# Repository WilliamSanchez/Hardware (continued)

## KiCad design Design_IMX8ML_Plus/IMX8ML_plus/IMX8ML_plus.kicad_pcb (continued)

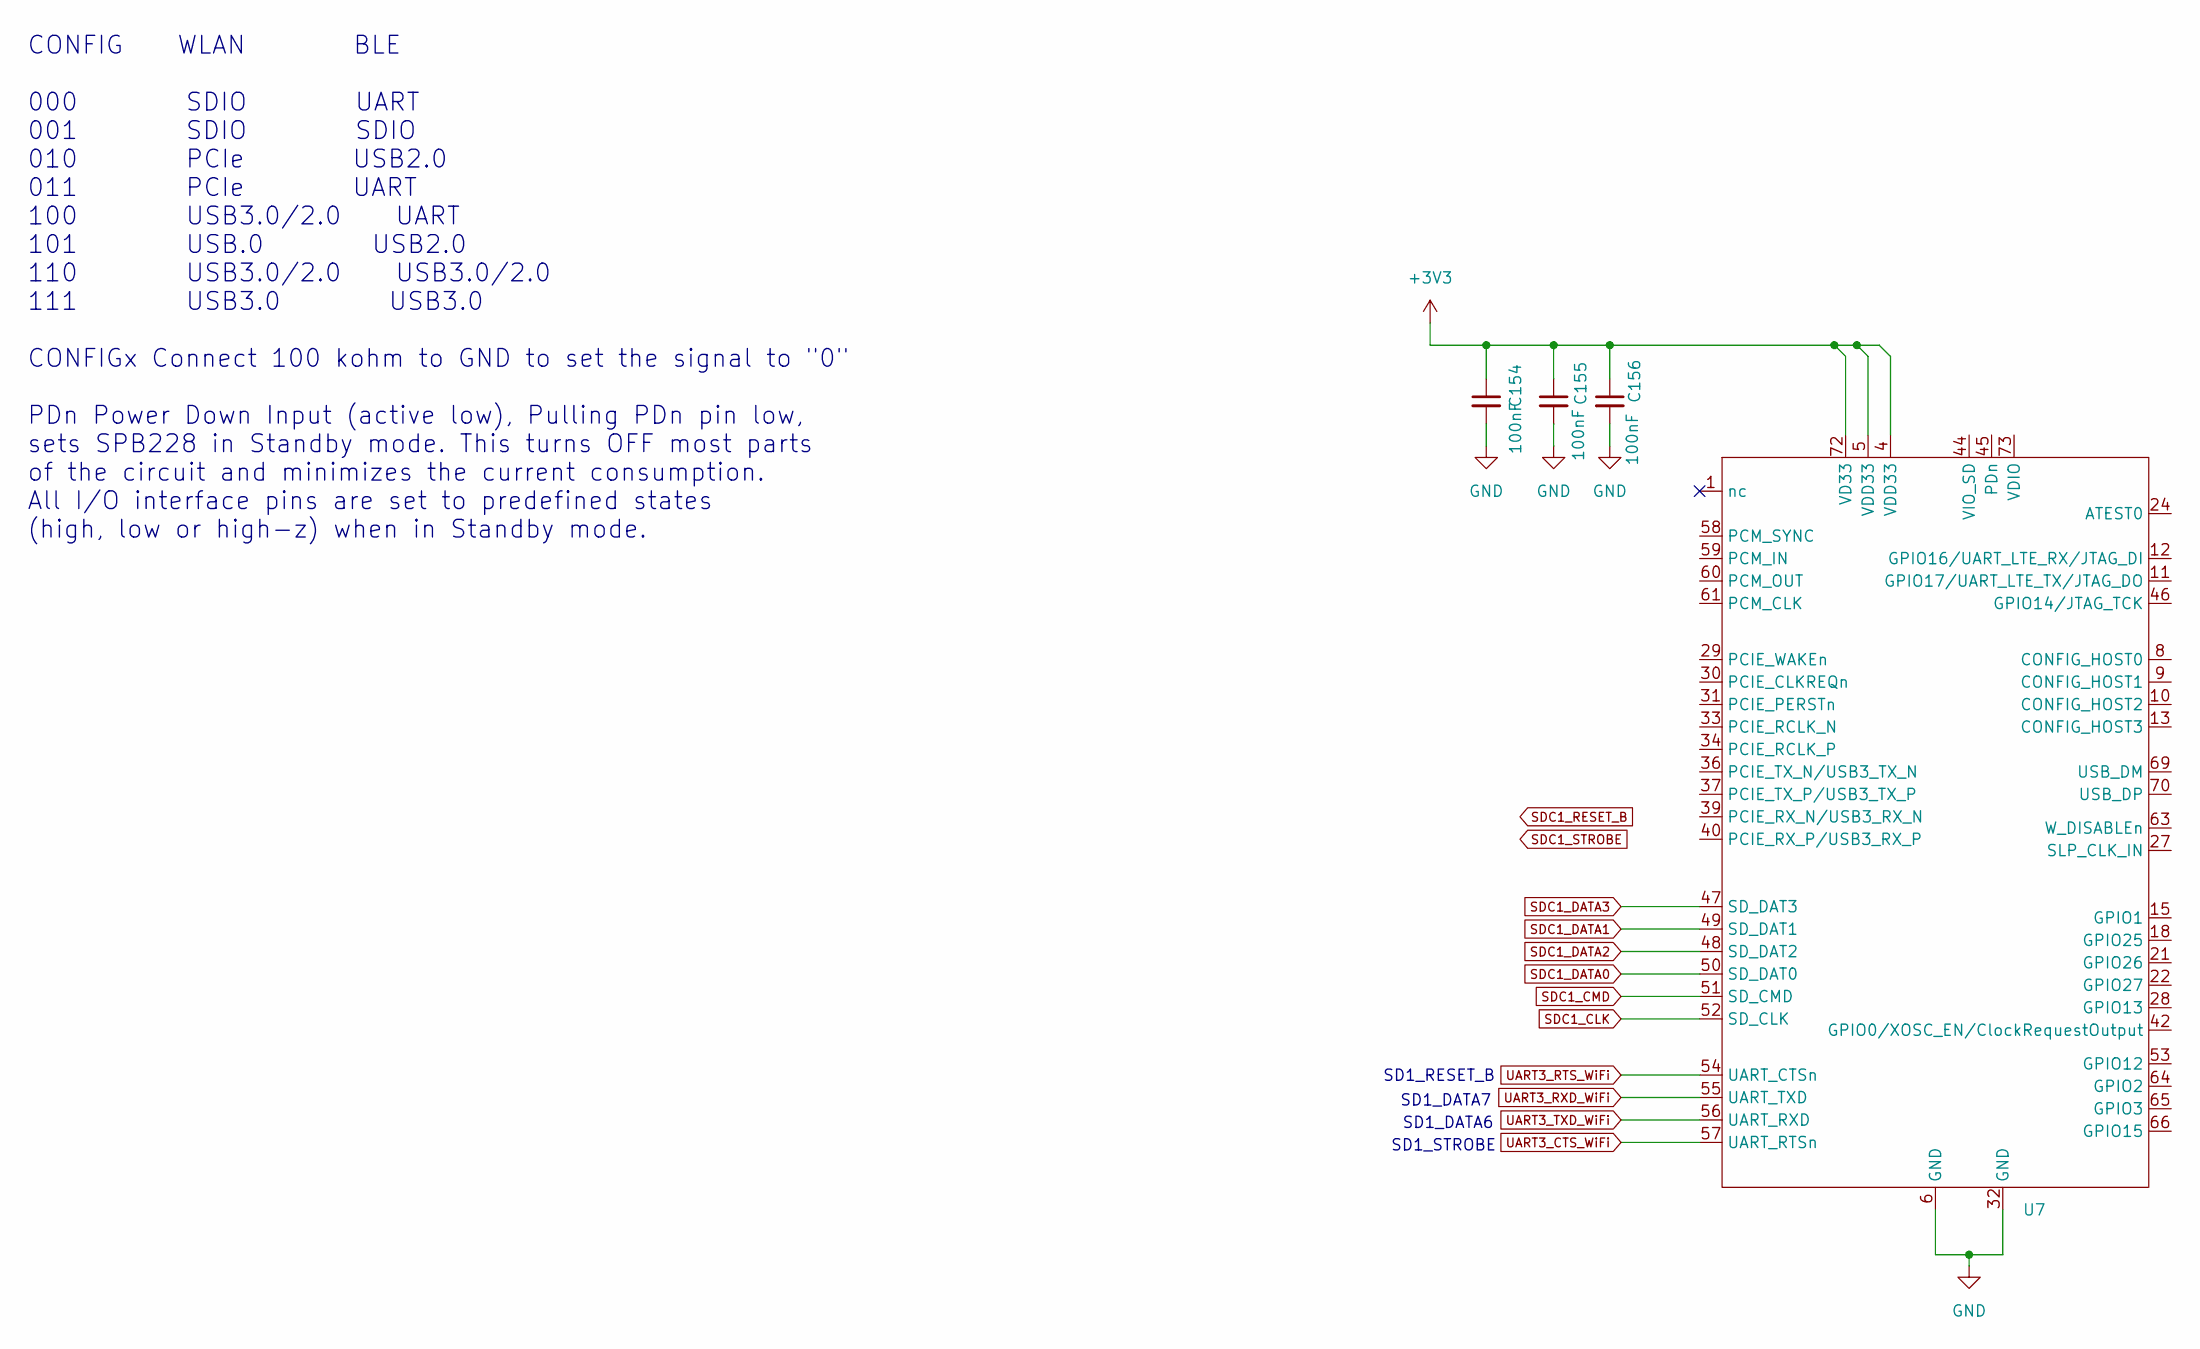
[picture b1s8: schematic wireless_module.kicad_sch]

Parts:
C154, C155, C156: 100nF; C_0201_0603Metric
U7: SPB228-QFN-96_11.55x15.55_Pitch0.5mm

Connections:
+3V3: C154.1, C155.1, C156.1, U7.4 (VDD33), U7.5 (VDD33), U7.72 (VD33); also elsewhere on the board
GND: C154.2, C155.2, C156.2, U7.6 (GND), U7.17 (GND), U7.20 (GND), U7.23 (GND), U7.26 (GND), U7.32 (GND), U7.35 (GND), U7.38 (GND), U7.41 (GND), U7.62 (GND), U7.68 (GND), U7.71 (GND), U7.74 (GND), U7.75 (GND), U7.76 (GND), U7.77 (GND), U7.78 (GND), U7.79 (GND), U7.80 (GND), U7.81 (GND), U7.82 (GND), U7.83 (GND), U7.84 (GND), U7.85 (GND), U7.86 (GND), U7.87 (GND), U7.89 (GND), U7.90 (GND), U7.91 (GND), U7.92 (GND), U7.93 (GND), U7.94 (GND), U7.95 (GND), U7.96 (GND); also elsewhere on the board
SDC1_CLK: U7.52 (SD_CLK); also elsewhere on the board
SDC1_CMD: U7.51 (SD_CMD); also elsewhere on the board
SDC1_DATA0: U7.50 (SD_DAT0); also elsewhere on the board
SDC1_DATA1: U7.49 (SD_DAT1); also elsewhere on the board
SDC1_DATA2: U7.48 (SD_DAT2); also elsewhere on the board
SDC1_DATA3: U7.47 (SD_DAT3); also elsewhere on the board
UART3_CTS_WiFi: U7.57 (UART_RTSn); also elsewhere on the board
UART3_RTS_WiFi: U7.54 (UART_CTSn); also elsewhere on the board
UART3_RXD_WiFi: U7.55 (UART_TXD); also elsewhere on the board
UART3_TXD_WiFi: U7.56 (UART_RXD); also elsewhere on the board

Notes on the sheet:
SD1_DATA7
SD1_RESET_B
SD1_STROBE
SD1_DATA6
CONFIG WLAN BLE 000 SDIO UART 001 SDIO SDIO 010 PCIe USB2.0 011 PCIe UART 100 USB3.0/2.0 UART 101 USB.0 USB2.0 110 USB3.0/2.0 USB3.0/2.0 111 USB3.0 USB3.0 CONFIGx Connect 100 kohm to GND to set the signal to "0" PDn Power Down Input (active low), Pulling PDn pin low, sets SPB228 in Standby mode. Th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

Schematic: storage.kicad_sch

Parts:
C115, C118: 12pF; C_0201_0603Metric
C116, C119, C120, C123, C124, C126, C127: 0.22uF; C_0201_0603Metric
C117: 1uF; C_0201_0603Metric
C121: 4.7uF; C_0402_1005Metric
C122, C125: 10uF; C_0402_1005Metric
C159, C160: 2200pF; C_0201_0603Metric
C161: 18pF; C_0201_0603Metric
D2: LED; LED_0603_1608Metric
Q1: NX3008NBKW,115; SOT-323_SC-70
R10, R11: 100K; R_0201_0603Metric
R12: 8.2K; R_0201_0603Metric
R13, R21: 100K; R_0402_1005Metric
R14: 4.7M; R_0402_1005Metric
R15: 10K; R_0402_1005Metric
R42: 0; R_0402_1005Metric
R43: 550; R_0402_1005Metric
U1: MIMX8ML8CVNKZAB; LFBGA548_SOT2047-1_NXP
U4: SDINBDG4-8G; BGA153C50P14X14_1300X1150X80N
U5: MT25QUxxxxxx1xW7; W-PDFN-8-1EP_6x5mm_P1.27mm_EP3x3mm
Y2: 32.768KHz; C_0504_1310Metric

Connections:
+3V3: R43.1; also elsewhere on the board
/Processor/storage/MIPI_TEST_DNU: C159.1, U1.F24 (MIPI_TEST_DNU)
/Processor/storage/MIPI_VREG1_CAP: C160.1, U1.F18 (MIPI_VREG1_CAP)
/Processor/storage/NAND_DQS: C161.1, R42.2, U1.R26 (NAND_DQS)
/Processor/storage/NAND_READY_B: Q1.1 (G), U1.T28 (NAND_READY_B)
/Processor/storage/QSPIA_DATA0: U1.R25 (NAND_DATA00), U5.5 (DQ0)
/Processor/storage/QSPIA_DATA1: U1.L25 (NAND_DATA01), U5.2 (DQ1)
/Processor/storage/QSPIA_DATA2: U1.L24 (NAND_DATA02), U5.3 (~W/DQ2)
/Processor/storage/QSPIA_DATA3: U1.N24 (NAND_DATA03), U5.7 (~RESET/DQ3)
/Processor/storage/QSPIA_SCLK: U1.N25 (NAND_ALE), U5.6 (C)
/Processor/storage/QSPIA_nSS0: R15.2, U1.L26 (NAND_CE0_B), U5.1 (~S)
/Processor/storage/SD3_CLK: U1.U29 (NAND_WP_B), U4.M6 (CLK)
/Processor/storage/SD3_CMD: U1.U28 (NAND_WE_B), U4.M5 (CMD)
/Processor/storage/SD3_DATA0: U1.P29 (NAND_DATA04), U4.A3 (DAT0)
/Processor/storage/SD3_DATA1: U1.N29 (NAND_DATA05), U4.A4 (DAT1)
/Processor/storage/SD3_DATA2: U1.M29 (NAND_DATA06), U4.A5 (DAT2)
/Processor/storage/SD3_DATA3: U1.R29 (NAND_DATA07), U4.B2 (DAT3)
/Processor/storage/SD3_DATA4: U1.R28 (NAND_RE_B), U4.B3 (DAT4)
/Processor/storage/SD3_DATA5: U1.P28 (NAND_CE2_B), U4.B4 (DAT5)
/Processor/storage/SD3_DATA6: U1.N28 (NAND_CE3_B), U4.B5 (DAT6)
/Processor/storage/SD3_DATA7: U1.M28 (NAND_CLE), U4.B6 (DAT7)
/Processor/storage/SD3_STROBE: U1.T29 (NAND_CE1_B), U4.H5 (RCLK)
CSI1_CLK_N: U1.E22 (MIPI_CSI1_CLK_N); also elsewhere on the board
CSI1_CLK_P: U1.D22 (MIPI_CSI1_CLK_P); also elsewhere on the board
CSI1_D0_N: U1.E18 (MIPI_CSI1_D0_N); also elsewhere on the board
CSI1_D0_P: U1.D18 (MIPI_CSI1_D0_P); also elsewhere on the board
CSI1_D1_N: U1.E20 (MIPI_CSI1_D1_N); also elsewhere on the board
CSI1_D1_P: U1.D20 (MIPI_CSI1_D1_P); also elsewhere on the board
CSI1_D2_N: U1.E24 (MIPI_CSI1_D2_N); also elsewhere on the board
CSI1_D2_P: U1.D24 (MIPI_CSI1_D2_P); also elsewhere on the board
CSI1_D3_N: U1.E26 (MIPI_CSI1_D3_N); also elsewhere on the board
CSI1_D3_P: U1.D26 (MIPI_CSI1_D3_P); also elsewhere on the board
CSI2_CLK_N: U1.B23 (MIPI_CSI2_CLK_N); also elsewhere on the board
CSI2_CLK_P: U1.A23 (MIPI_CSI2_CLK_P); also elsewhere on the board
CSI2_D0_N: U1.B25 (MIPI_CSI2_D0_N); also elsewhere on the board
CSI2_D0_P: U1.A25 (MIPI_CSI2_D0_P); also elsewhere on the board
CSI2_D1_N: U1.B24 (MIPI_CSI2_D1_N); also elsewhere on the board
CSI2_D1_P: U1.A24 (MIPI_CSI2_D1_P); also elsewhere on the board
CSI2_D2_N: U1.B22 (MIPI_CSI2_D2_N); also elsewhere on the board
CSI2_D2_P: U1.A22 (MIPI_CSI2_D2_P); also elsewhere on the board
CSI2_D3_N: U1.B21 (MIPI_CSI2_D3_N); also elsewhere on the board
CSI2_D3_P: U1.A21 (MIPI_CSI2_D3_P); also elsewhere on the board
DSI1_CLK_N: U1.B18 (MIPI_DSI1_CLK_N); also elsewhere on the board
DSI1_CLK_P: U1.A18 (MIPI_DSI1_CLK_P); also elsewhere on the board
DSI1_D0_N: U1.B16 (MIPI_DSI1_D0_N); also elsewhere on the board
DSI1_D0_P: U1.A16 (MIPI_DSI1_D0_P); also elsewhere on the board
DSI1_D1_N: U1.B17 (MIPI_DSI1_D1_N); also elsewhere on the board
DSI1_D1_P: U1.A17 (MIPI_DSI1_D1_P); also elsewhere on the board
DSI1_D2_N: U1.B19 (MIPI_DSI1_D2_N); also elsewhere on the board
DSI1_D2_P: U1.A19 (MIPI_DSI1_D2_P); also elsewhere on the board
DSI1_D3_N: U1.B20 (MIPI_DSI1_D3_N); also elsewhere on the board
DSI1_D3_P: U1.A20 (MIPI_DSI1_D3_P); also elsewhere on the board
GND: C115.2, C116.2, C117.2, C118.2, C119.2, C120.2, C121.2, C122.2, C123.2, C124.2, C125.2, C126.2, C127.2, C159.2, C160.2, C161.2, Q1.2 (S), R10.2, R12.2, U4.A6 (VSS_A6), U4.C4 (VSSQ_C4), U4.E7 (VSS_E7), U4.G5 (VSS_G5), U4.H10 (VSS_H10), U4.J5 (VSS_J5), U4.K8 (VSS_K8), U4.N2 (VSSQ_N2), U4.N5 (VSSQ_N5), U4.P4 (VSSQ_P4), U4.P6 (VSSQ_P6), U5.4 (VSS), U5.9 (PAD); also elsewhere on the board
LP4_VDD1: C122.1, C123.1, C124.1, C125.1, C126.1, C127.1, R15.1, U1.U24 (NVCC_SD1), U4.C6 (VCCQ_C6), U4.M4 (VCCQ_M4), U4.N4 (VCCQ_N4), U4.P3 (VCCQ_P3), U4.P5 (VCCQ_P5), U5.8 (VCC); also elsewhere on the board
NAND_DQS_PINOUT: R42.1
NVCC_SD2: U1.W24 (NVCC_SD2); also elsewhere on the board
NVCC_SNVS_1V8: R11.1, R13.1, R21.1; also elsewhere on the board
unnamed: D2.2 (A), R43.2
unnamed: D2.1 (K), Q1.3 (D)
unnamed: R12.1, U1.F16 (PCIE_RESREF)
unnamed: C118.1, R14.1, U1.J25 (RTC_XTALI), Y2.1
unnamed: C115.1, R14.2, U1.J26 (RTC_XTALO), Y2.2
unnamed: C117.1, C120.1, U4.C2 (VDDI)
ON/OFF: R11.2, U1.G22 (ONOFF); also elsewhere on the board
PCIE_REF_PAD_CLK_N: U1.E16 (PCIE_REF_PAD_CLK_N); also elsewhere on the board
PCIE_REF_PAD_CLK_P: U1.D16 (PCIE_REF_PAD_CLK_P); also elsewhere on the board
PCIE_RXN_N: U1.B14 (PCIE_RXN_N); also elsewhere on the board
PCIE_RXN_P: U1.A14 (PCIE_RXN_P); also elsewhere on the board
PCIE_TXN_N: U1.B15 (PCIE_TXN_N); also elsewhere on the board
PCIE_TXN_P: U1.A15 (PCIE_TXN_P); also elsewhere on the board
PMIC_ON_REQ: R13.2, U1.F22 (PMIC_ON_REQ); also elsewhere on the board
PMIC_STBY_REC: R10.1, U1.J24 (PMIC_STBY_REQ); also elsewhere on the board
PM_VDD_3V3: C116.1, C119.1, C121.1, U4.E6 (VCC_E6), U4.F5 (VCC_F5), U4.J10 (VCC_J10), U4.K9 (VCC_K9); also elsewhere on the board
POR_B: R21.2, U1.J29 (POR_B); also elsewhere on the board
SAI1_MCLK: U1.AE12 (SAI1_MCLK); also elsewhere on the board
SAI1_RXC: U1.AH8 (SAI1_RXC); also elsewhere on the board
SAI1_RXFS: U1.AJ9 (SAI1_RXFS); also elsewhere on the board
SAI1_TXC: U1.AJ12 (SAI1_TXC); also elsewhere on the board
SAI1_TXFS: U1.AF12 (SAI1_TXFS); also elsewhere on the board

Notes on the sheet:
SAI1_TXFS ETH_2_RGMII_RX_CTL SAI1_TXC ETH_2_RGMII_RXC
ON/OFF[G22] PinOUT(BUTTON) POR_B [J29] PMIC PMIC_ON_REQ [F22] PMI PMIC_STBY_REQ [J24] PMIC

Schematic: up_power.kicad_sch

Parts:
U1: MIMX8ML8CVNKZAB; LFBGA548_SOT2047-1_NXP

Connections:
GND: U1.A1 (VSS), U1.A29 (VSS), U1.AA3 (VSS), U1.AA7 (VSS), U1.AA23 (VSS), U1.AA27 (VSS), U1.AB8 (VSS), U1.AB10 (VSS), U1.AB12 (VSS), U1.AB14 (VSS), U1.AB16 (VSS), U1.AB18 (VSS), U1.AB20 (VSS), U1.AB22 (VSS), U1.AC3 (VSS), U1.AC6 (VSS), U1.AC24 (VSS), U1.AC27 (VSS), U1.AE3 (VSS), U1.AE27 (VSS), U1.AG4 (VSS), U1.AG6 (VSS), U1.AG8 (VSS), U1.AG10 (VSS), U1.AG12 (VSS), U1.AG14 (VSS), U1.AG16 (VSS), U1.AG18 (VSS), U1.AG20 (VSS), U1.AG22 (VSS), U1.AG24 (VSS), U1.AG26 (VSS), U1.AJ1 (VSS), U1.AJ29 (VSS), U1.C4 (VSS), U1.C6 (VSS), U1.C8 (VSS), U1.C10 (VSS), U1.C12 (VSS), U1.C14 (VSS), U1.C16 (VSS), U1.C18 (VSS), U1.C20 (VSS), U1.C22 (VSS), U1.C24 (VSS), U1.C26 (VSS), U1.E3 (VSS), U1.E27 (VSS), U1.G3 (VSS), U1.G6 (VSS), U1.G24 (VSS), U1.G27 (VSS), U1.H8 (VSS), U1.H10 (VSS), U1.H12 (VSS), U1.H14 (VSS), U1.H16 (VSS), U1.H18 (VSS), U1.H20 (VSS), U1.H22 (VSS), U1.J3 (VSS), U1.J7 (VSS), U1.J23 (VSS), U1.J27 (VSS), U1.L3 (VSS), U1.L7 (VSS), U1.L14 (VSS), U1.L16 (VSS), U1.L23 (VSS), U1.L27 (VSS), U1.M11 (VSS), U1.M19 (VSS), U1.N3 (VSS), U1.N7 (VSS), U1.N11 (VSS), U1.N19 (VSS), U1.N23 (VSS), U1.N27 (VSS), U1.P11 (VSS), U1.P19 (VSS), U1.R3 (VSS), U1.R7 (VSS), U1.R11 (VSS), U1.R12 (VSS), U1.R13 (VSS), U1.R14 (VSS), U1.R16 (VSS), U1.R17 (VSS), U1.R18 (VSS), U1.R19 (VSS), U1.R23 (VSS), U1.R27 (VSS), U1.T11 (VSS), U1.T19 (VSS), U1.U3 (VSS), U1.U7 (VSS), U1.U11 (VSS), U1.U18 (VSS), U1.U19 (VSS), U1.U23 (VSS), U1.U27 (VSS), U1.V11 (VSS), U1.V19 (VSS), U1.W3 (VSS), U1.W7 (VSS), U1.W14 (VSS), U1.W16 (VSS), U1.W23 (VSS), U1.W27 (VSS); also elsewhere on the board
LP4_VDD1: U1.AA11 (NVCC_SAI2_SAI3_SPDIF), U1.AA14 (NVCC_ECSPI_HDMI), U1.AA16 (PVCC2_1P8), U1.AA19 (PVCC1_1P8), U1.AA24 (NVCC_ENET), U1.J11 (NVCC_GPIO), U1.J16 (PVCC0_1P8), U1.K11 (NVCC_JTAG), U1.R22 (NVCC_CLK), U1.U22 (NVCC_NAND), U1.Y10 (NVCC_I2C_UART), U1.Y11 (NVCC_SAI1_SAI5); also elsewhere on the board
LP4_VDD2: U1.AA8 (NVCC_DRAM), U1.AA10 (NVCC_DRAM), U1.J8 (NVCC_DRAM), U1.J10 (NVCC_DRAM), U1.L8 (NVCC_DRAM), U1.N8 (NVCC_DRAM), U1.R8 (NVCC_DRAM), U1.U8 (NVCC_DRAM), U1.W8 (NVCC_DRAM); also elsewhere on the board
NVCC_SNVS_1V8: U1.R24 (NVCC_SNVS_1P8); also elsewhere on the board
PM_VDDA_1V8: U1.AA20 (VDD_EARC_1P8), U1.AA22 (VDD_HDMI_1P8), U1.J19 (VDD_USB_1P8), U1.J20 (VDD_ANA0_1P8), U1.J22 (VDD_LVDS_1P8), U1.K19 (VDD_PCI_1P8), U1.K20 (VDD_MIPI_1P8), U1.L22 (VDD_24M_XTAL_1P8), U1.N22 (VDD_ANA1_1P8), U1.R6 (VDD_DRAM_PLL_1P8), U1.W18 (VDD_SAI_PLL_1P8), U1.W19 (VDD_AVPLL_1P8), U1.Y19 (VDD_ARM_PLL_1P8), U1.Y20 (VDD_ANA2_1P8); also elsewhere on the board
PM_VDD_3V3: U1.J14 (VDD_USB_3P3); also elsewhere on the board
PM_VDD_ARM: U1.T14 (VDD_ARM), U1.T16 (VDD_ARM), U1.U12 (VDD_ARM), U1.U13 (VDD_ARM), U1.U14 (VDD_ARM), U1.U15 (VDD_ARM), U1.U16 (VDD_ARM), U1.U17 (VDD_ARM), U1.V14 (VDD_ARM), U1.V16 (VDD_ARM), U1.W12 (VDD_ARM), U1.W13 (VDD_ARM), U1.W17 (VDD_ARM), U1.Y14 (VDD_ARM), U1.Y15 (VDD_ARM), U1.Y16 (VDD_ARM); also elsewhere on the board
PM_VDD_SoC: U1.K10 (VDD_SOC), U1.K14 (VDD_USB_0P8), U1.K15 (VDD_PCI_0P8), U1.K16 (VDD_MIPI_0P8), U1.L9 (VDD_SOC), U1.L10 (VDD_SOC), U1.L11 (VDD_SOC), U1.L12 (VDD_SOC), U1.L13 (VDD_SOC), U1.L17 (VDD_SOC), U1.L18 (VDD_SOC), U1.L19 (VDD_SOC), U1.L20 (VDD_SOC), U1.L21 (VDD_SOC), U1.M14 (VDD_SOC), U1.M16 (VDD_SOC), U1.N9 (VDD_SOC), U1.N10 (VDD_SOC), U1.N12 (VDD_SOC), U1.N13 (VDD_SOC), U1.N14 (VDD_SOC), U1.N15 (VDD_SOC), U1.N16 (VDD_SOC), U1.N17 (VDD_SOC), U1.N18 (VDD_SOC), U1.N20 (VDD_SOC), U1.N21 (VDD_SOC), U1.N26 (VDD_SNVS_0P8_CAP), U1.P14 (VDD_SOC), U1.P16 (VDD_SOC), U1.R9 (VDD_DRAM_PLL_0P8), U1.R10 (VDD_SOC), U1.R20 (VDD_SOC), U1.R21 (VDD_ANA1_0P8), U1.U9 (VDD_SOC), U1.U10 (VDD_SOC), U1.U20 (VDD_SOC), U1.U21 (VDD_SAI_PLL_0P8), U1.W9 (VDD_SOC), U1.W10 (VDD_SOC), U1.W11 (VDD_SOC), U1.W20 (VDD_SOC), U1.W21 (VDD_ARM_PLL_0P8), U1.W22 (VDD_HDMI_0P8); also elsewhere on the board

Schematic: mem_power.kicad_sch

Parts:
C30, C31, C36, C37, C38: 10uF; C_0402_1005Metric
C32, C33, C34, C35, C39, C40, C41, C42, C43, C44, C45, C46, C47, C48, C49, C50, C51: 1uF; C_0201_0603Metric

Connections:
GND: C30.2, C31.2, C32.2, C33.2, C34.2, C35.2, C36.2, C37.2, C38.2, C39.2, C40.2, C41.2, C42.2, C43.2, C44.2, C45.2, C46.2, C47.2, C48.2, C49.2, C50.2, C51.2; also elsewhere on the board
LP4_VDD1: C30.1, C31.1, C32.1, C33.1, C34.1, C35.1; also elsewhere on the board
LP4_VDD2: C36.1, C37.1, C38.1, C39.1, C40.1, C41.1, C42.1, C43.1, C44.1, C45.1, C46.1, C47.1, C48.1, C49.1, C50.1, C51.1; also elsewhere on the board

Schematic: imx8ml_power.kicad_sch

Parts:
C52, C53, C55, C56, C58, C59, C62, C66, C81, C104: 10uF; C_0402_1005Metric
C54, C57, C60, C61, C63, C64, C65, C67, C68, C69, C70, C71, C72, C73, C74, C75, C76, C77, C78, C79, C80, C82, C83, C84, C85, C86, C87, C88, C89, C90, C91, C92, C93, C94, C95, C96, C97, C98, C99, C100, C101, C102, C103, C105, C107, C108, C109, C110, C111, C112, C114: 1uF; C_0201_0603Metric
C106, C113: 0.22uF; C_0201_0603Metric

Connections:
GND: C52.2, C53.2, C54.2, C55.2, C56.2, C57.2, C58.2, C59.2, C60.2, C61.2, C62.2, C63.2, C64.2, C65.2, C66.2, C67.2, C68.2, C69.2, C70.2, C71.2, C72.2, C73.2, C74.2, C75.2, C76.2, C77.2, C78.2, C79.2, C80.2, C81.2, C82.2, C83.2, C84.2, C85.2, C86.2, C87.2, C88.2, C89.2, C90.2, C91.2, C92.2, C93.2, C94.2, C95.2, C96.2, C97.2, C98.2, C99.2, C100.2, C101.2, C102.2, C103.2, C104.2, C105.2, C106.2, C107.2, C108.2, C109.2, C110.2, C111.2, C112.2, C113.2, C114.2; also elsewhere on the board
LP4_VDD1: C104.1, C105.1, C107.1, C108.1, C109.1, C110.1, C111.1, C112.1, C114.1; also elsewhere on the board
LP4_VDD2: C55.1, C59.1, C63.1, C67.1, C70.1, C73.1, C76.1, C79.1, C84.1; also elsewhere on the board
NVCC_SD2: C113.1; also elsewhere on the board
NVCC_SNVS_1V8: C96.1; also elsewhere on the board
PM_VDDA_1V8: C81.1, C82.1, C87.1, C89.1, C91.1, C93.1, C95.1, C98.1, C100.1, C102.1; also elsewhere on the board
PM_VDD_3V3: C106.1; also elsewhere on the board
PM_VDD_ARM: C52.1, C56.1, C61.1, C65.1, C68.1, C71.1, C74.1, C77.1, C80.1, C85.1; also elsewhere on the board
PM_VDD_SoC: C53.1, C54.1, C57.1, C58.1, C60.1, C62.1, C64.1, C66.1, C69.1, C72.1, C75.1, C78.1, C83.1, C86.1, C88.1, C90.1, C92.1, C94.1, C97.1, C99.1, C101.1, C103.1; also elsewhere on the board

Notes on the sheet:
PinOut
VSD_3v3
GPIO

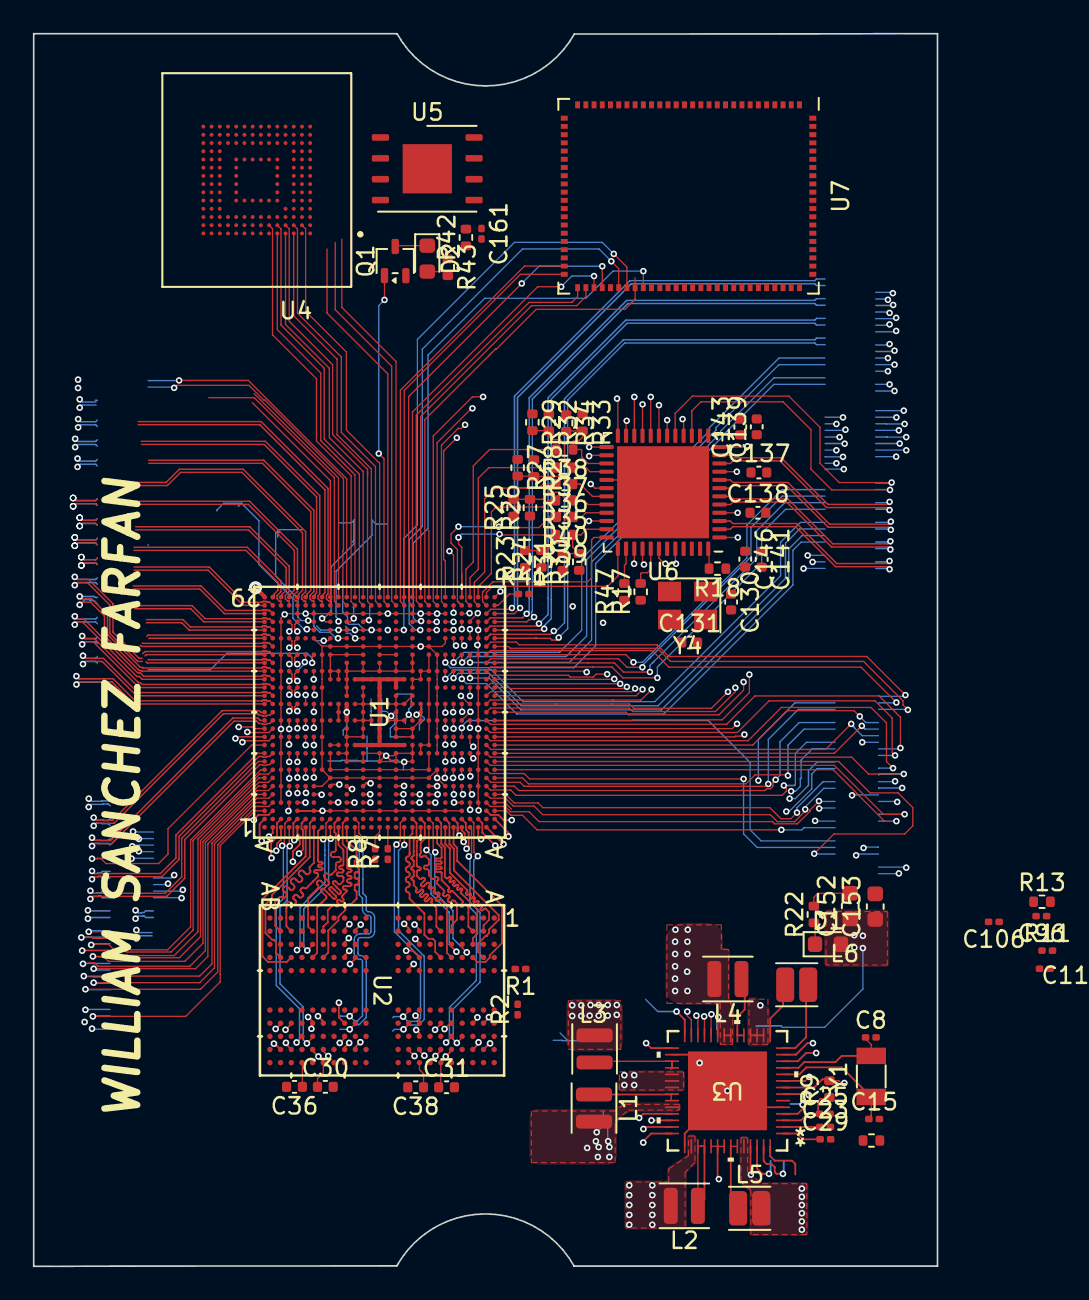
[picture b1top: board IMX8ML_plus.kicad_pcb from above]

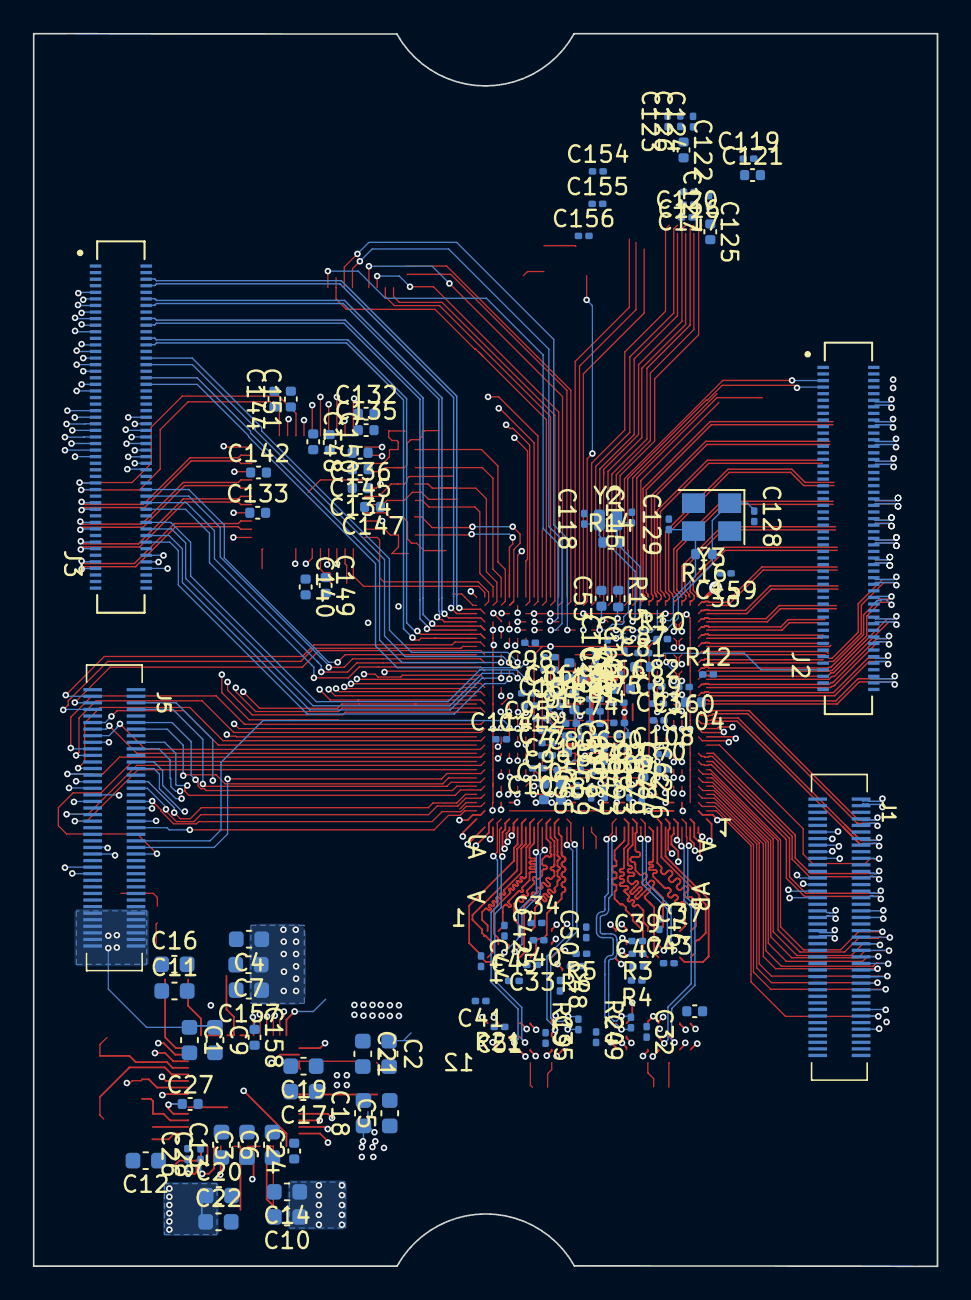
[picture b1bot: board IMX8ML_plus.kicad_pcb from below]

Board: 8 copper layers, 55.0 x 75.0 mm, 229 parts (155 on the bottom side), 372 nets.

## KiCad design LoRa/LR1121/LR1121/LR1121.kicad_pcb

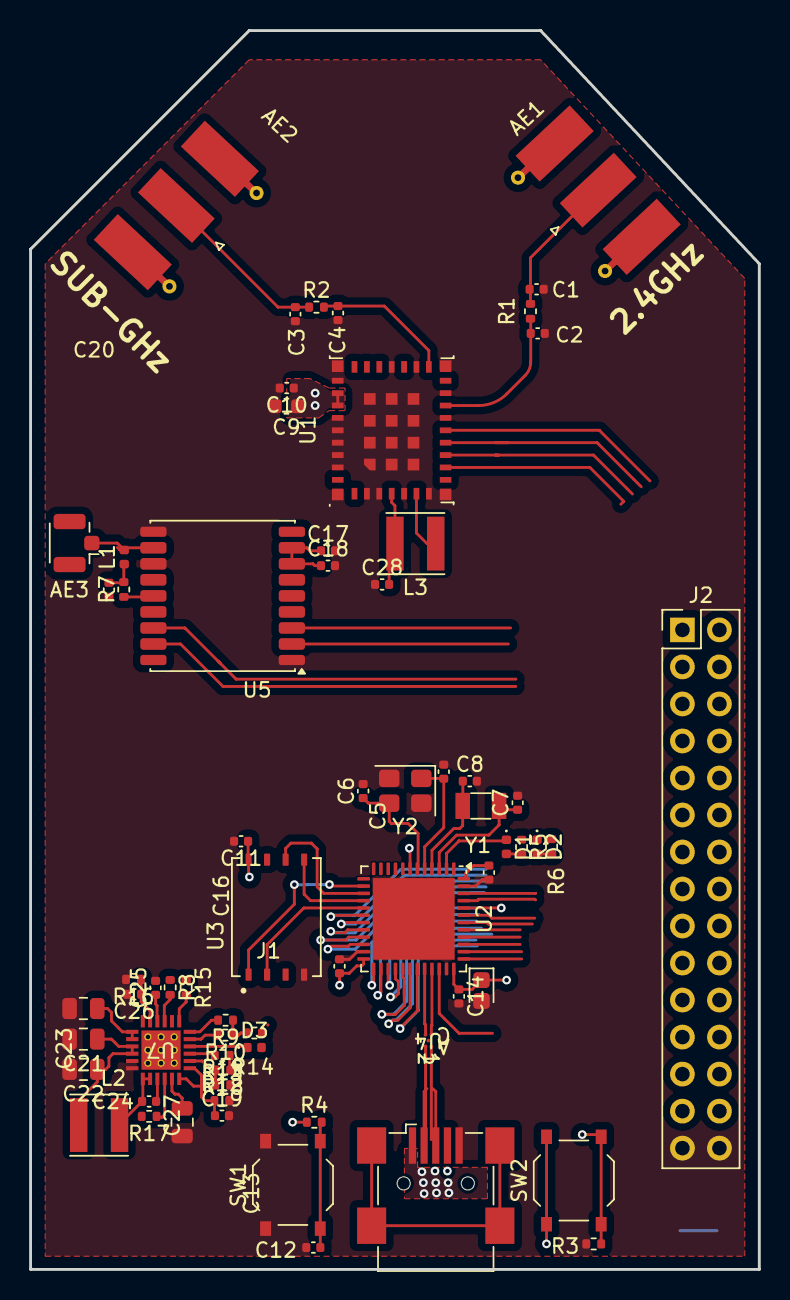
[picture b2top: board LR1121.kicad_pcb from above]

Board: 4 copper layers, 50.0 x 85.0 mm, 68 parts (1 on the bottom side), 62 nets.

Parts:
AE1: 2.4Gz; SMA_Molex_73251-1153_EdgeMount_Horizontal
AE2: SUB-GHz; SMA_Molex_73251-1153_EdgeMount_Horizontal
AE3: GPS; U.FL_Hirose_U.FL-R-SMT-1_Vertical
C1, C2, C3, C4: NU; C_0402_1005Metric
C5, C6, C7, C8: 12pF; C_0402_1005Metric
C9: 10uF; C_0603_1608Metric
C10, C11, C12, C14, C15, C16, C17, C18, C20: 100nF; C_0402_1005Metric
C13: 2.2uF; CP_EIA-1608-08_AVX-J
C19: 1uF; C_0402_1005Metric
C21, C22, C23, C27: 10uF; C_0805_2012Metric
C24: 0.047uF; C_0402_1005Metric
C25, C26: 0.1uF; C_0402_1005Metric
C28: 470nF; C_0402_1005Metric
D1, D3: GREEN; LED_0402_1005Metric
D2: RED; LED_0402_1005Metric
J1: USB_B_Micro; USB_Mini-B_Wuerth_65100516121_Horizontal
J2: PinOUT; PinHeader_2x15_P2.54mm_Vertical
L1: 27nH; L_0402_1005Metric
L2: 2.2uH; L_Taiyo-Yuden_MD-4040
L3: 15uH; L_Taiyo-Yuden_MD-4040
R1, R2, R19: 0; R_0402_1005Metric
R3, R8, R9, R10, R12, R15, R16, R17: 10K; R_0402_1005Metric
R4, R5, R6, R7: 100; R_0402_1005Metric
R11: 0.01; R_2010_5025Metric
R13, R18: 2.21K; R_0402_1005Metric
R14: 2.2K; R_0402_1005Metric
SW1: NRST; SW_Push_1P1T_XKB_TS-1187A
SW2: BOOT0; SW_Push_1P1T_XKB_TS-1187A
U1: LBAA0XV2GT
U2: STM32L552CCUx; QFN-48-1EP_7x7mm_P0.5mm_EP5.6x5.6mm
U3: MT29F4G01ABAFDWB-IT:F TR; SON127P600X800X65-8N
U4: PCMF1USB3S; WLCSP52-1-2_NEX
U5: MAX-M10S; ublox_MAX
U7: BQ25619ERTWR
Y1: 32.768KHz; Crystal_SMD_3215-2Pin_3.2x1.5mm
Y2: 25MHz; Crystal_SMD_3225-4Pin_3.2x2.5mm

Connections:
+3.3V: C9.1, C10.1, C11.1, C13.1, C14.1, C15.1, C16.1, C17.1, C18.1, J2.1, J2.2, R4.1, R5.1, R6.1, SW2.1 (A), U1.28 (VDD), U1.29 (VDD), U2.24 (VDD), U2.36 (VDD), U2.48 (VDD), U3.8 (VCC), U5.7 (VCC_IO), U5.8 (VCC)
/LoRa-system/ComunicationUnit/VREG: C28.2, L3.2, U1.4 (VREG)
/LoRa-system/ControlUnit/BOOT0: R3.1, SW2.2 (B), U2.44 (PH3)
/LoRa-system/ControlUnit/D1: D1.1 (K), U2.2 (PC13)
/LoRa-system/ControlUnit/MCU_Rx: J2.14, U2.12 (PA2)
/LoRa-system/ControlUnit/MCU_Tx: J2.16, U2.13 (PA3)
/LoRa-system/ControlUnit/Mem_MISO: U2.16 (PA6), U3.5 (MOSI)
/LoRa-system/ControlUnit/Mem_MOSI: U2.17 (PA7), U3.2 (MISO)
/LoRa-system/ControlUnit/Mem_NSS: U2.14 (PA4), U3.1 (~CS)
/LoRa-system/ControlUnit/Mem_SCK: U2.15 (PA5), U3.6 (SCK)
/LoRa-system/ControlUnit/NRST: C12.1, R4.2, SW1.2 (B), U2.7 (NRST)
/LoRa-system/ControlUnit/PC14: C7.1, U2.3 (PC14), Y1.2
/LoRa-system/ControlUnit/PC15: C8.1, U2.4 (PC15), Y1.1
/LoRa-system/ControlUnit/PH0: C5.1, U2.5 (PH0), Y2.1
/LoRa-system/ControlUnit/PH1: C6.1, U2.6 (PH1), Y2.3
/LoRa-system/ControlUnit/USB_D+: U2.33 (PA12), U4.C1 (CH1_OUT+)
/LoRa-system/ControlUnit/USB_D-: U2.32 (PA11), U4.C2 (CH1_OUT-)
/LoRa-system/PowerUnit/3V3: R8.1, R9.1, R10.1, R14.1, R15.1
/LoRa-system/PowerUnit/INT_N: R15.2, U7.7 (INT_N)
/LoRa-system/PowerUnit/PMIC_CE#: R8.2, U7.9 (CE_N)
/LoRa-system/PowerUnit/PMID: C27.1, U7.23 (PMID)
/LoRa-system/PowerUnit/PMID_GOOD: R13.2, U7.3 (PMID_GOOD)
/LoRa-system/PowerUnit/PSEL: R18.2, R19.1, U7.2 (PSEL)
/LoRa-system/PowerUnit/REGN: R13.1, R17.1, R18.1, U7.22 (REGN)
/LoRa-system/PowerUnit/STAT: D3.1 (K), U7.4 (STAT)
/LoRa-system/PowerUnit/TS: C26.1, R16.1, R17.2, U7.11 (TS)
/LoRa-system/PowerUnit/V_SYS: C21.1, C22.1, L2.1, U7.15 (SYS), U7.16 (SYS)
GND: C1.2, C2.2, C3.2, C4.2, C5.2, C6.2, C7.2, C8.2, C9.2, C10.2, C11.2, C12.2, C13.2, C14.2, C15.2, C16.2, C17.2, C18.2, C19.2, C20.2, C21.2, C22.2, C23.2, C25.2, C26.2, C27.2, C28.1, J1.5 (GND), J2.29, J2.30, R3.2, R12.2, R16.2, R19.2, SW1.1 (A), U1.2 (DIO8), U1.3 (GND), U1.5 (GND), U1.7 (GND), U1.8 (GND), U1.14 (GND), U1.16 (GND), U1.18 (GND), U1.20 (GND), U1.22 (GND), U1.26 (GND), U1.27 (GND), U1.30 (GND), U1.31 (GND), U1.32 (GND), U1.33 (GND), U1.34 (GND), U1.36 (GND), U1.37 (GND), U1.38 (GND), U1.39 (GND), U1.40 (GND), U1.41 (GND), U1.42 (GND), U1.43 (GND), U1.44 (GND), U1.45 (GND), U1.46 (GND), U1.47 (GND), U1.48 (GND), U2.23 (VSS), U2.35 (VSS), U2.47 (VSS), U2.49 (VSS), U3.4 (GND), U4.B1 (GND_CH1), U5.1 (GND), U5.10 (GND), U5.12 (GND), U7.17 (PGND), U7.18 (PGND), U7.25 (PAD), Y2.2, Y2.4
GPS_RX: J2.13, U5.3 (RXD)
GPS_TX: J2.15, U5.2 (TXD)
I2CSCL_GPS: J2.3, R10.2, U2.43 (PB7), U5.17 (SCL), U7.5 (SCL)
I2CSDA_GPS: J2.5, R9.2, U2.42 (PB6), U5.16 (SDA), U7.6 (SDA)
LoRa_MISO: J2.11, U1.11 (LR_MISO), U2.27 (PB14)
LoRa_MOSI: J2.9, U1.12 (LR_MOSI), U2.28 (PB15)
LoRa_NSS: U1.10 (LR_NSS), U2.25 (PB12)
LoRa_SCK: J2.7, U1.13 (LR_SCK), U2.26 (PB13)
unnamed: AE1.1 (A), C1.1, R1.1
unnamed: AE2.1 (A), C3.1, R2.1
unnamed: AE3.1 (A), L1.2, U5.11 (RF_IN)
unnamed: C20.1, L1.1, R7.2
unnamed: C24.1, L2.2, U7.19 (SW), U7.20 (SW)
unnamed: D1.2 (A), R5.2
unnamed: D2.2 (A), R6.2
unnamed: D3.2 (A), R14.2
unnamed: J1.3 (D+), U4.A1 (CH1_IN+)
unnamed: J1.2 (D-), U4.A2 (CH1_IN-)
unnamed: C23.1, C25.1, U7.10 (BATSNS), U7.13 (BAT), U7.14 (BAT)
unnamed: C2.1, R1.2, U1.15 (ANT_LORA_2.4G)
unnamed: C4.1, R2.2, U1.19 (ANT_LORA_SUB-G)
unnamed: L3.1, U1.6 (DCC_SW)
unnamed: R7.1, U5.14 (VCC_RF)
unnamed: C24.2, U7.21 (BTST)
unnamed: C19.1, R11.2, R12.1, U7.1 (VAC), U7.24 (VBUS)
PA0: J2.4, U2.10 (PA0)
PA1: J2.6, U2.11 (PA1)
PA8: J2.18, U2.29 (PA8)
PA9: J2.20, U2.30 (PA9)
PA10: J2.22, U2.31 (PA10)
PA13: J2.24, U2.34 (PA13)
PA14: J2.26, U2.37 (PA14)
PA15: J2.28, U2.38 (PA15)
V_IN: J1.1 (VBUS), R11.1

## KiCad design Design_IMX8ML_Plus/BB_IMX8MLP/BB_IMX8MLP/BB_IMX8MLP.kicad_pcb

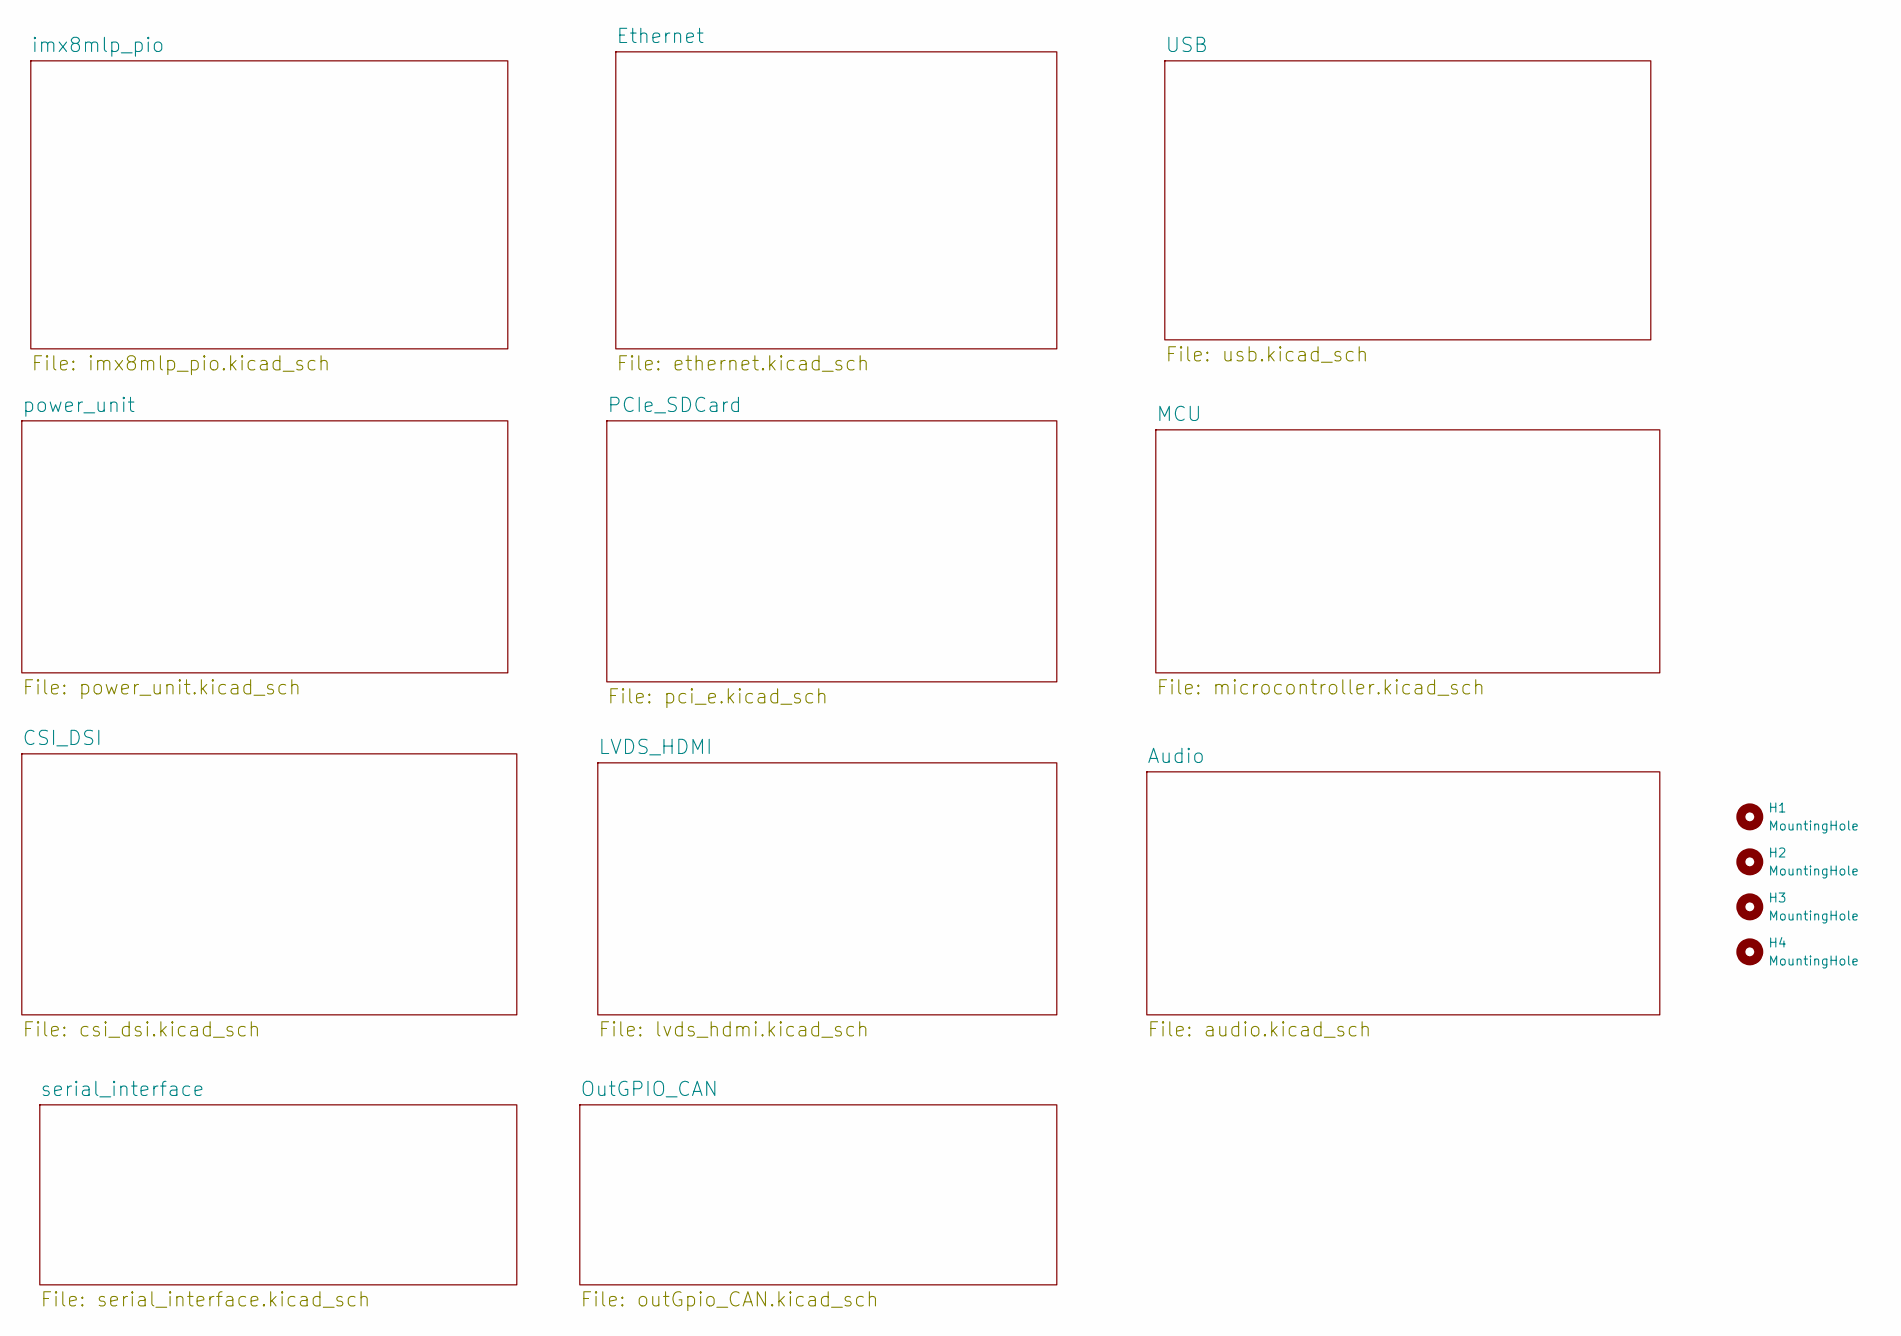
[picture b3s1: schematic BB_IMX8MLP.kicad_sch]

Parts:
H1, H2, H3, H4: MountingHole; MountingHole_4.5mm_Pad
